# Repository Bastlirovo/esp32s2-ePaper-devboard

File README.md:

# esp32s2-ePaper-devboard
Development board for ESP32-S2, with two LDO options, two Li-ion charger options and ePaper connection part.

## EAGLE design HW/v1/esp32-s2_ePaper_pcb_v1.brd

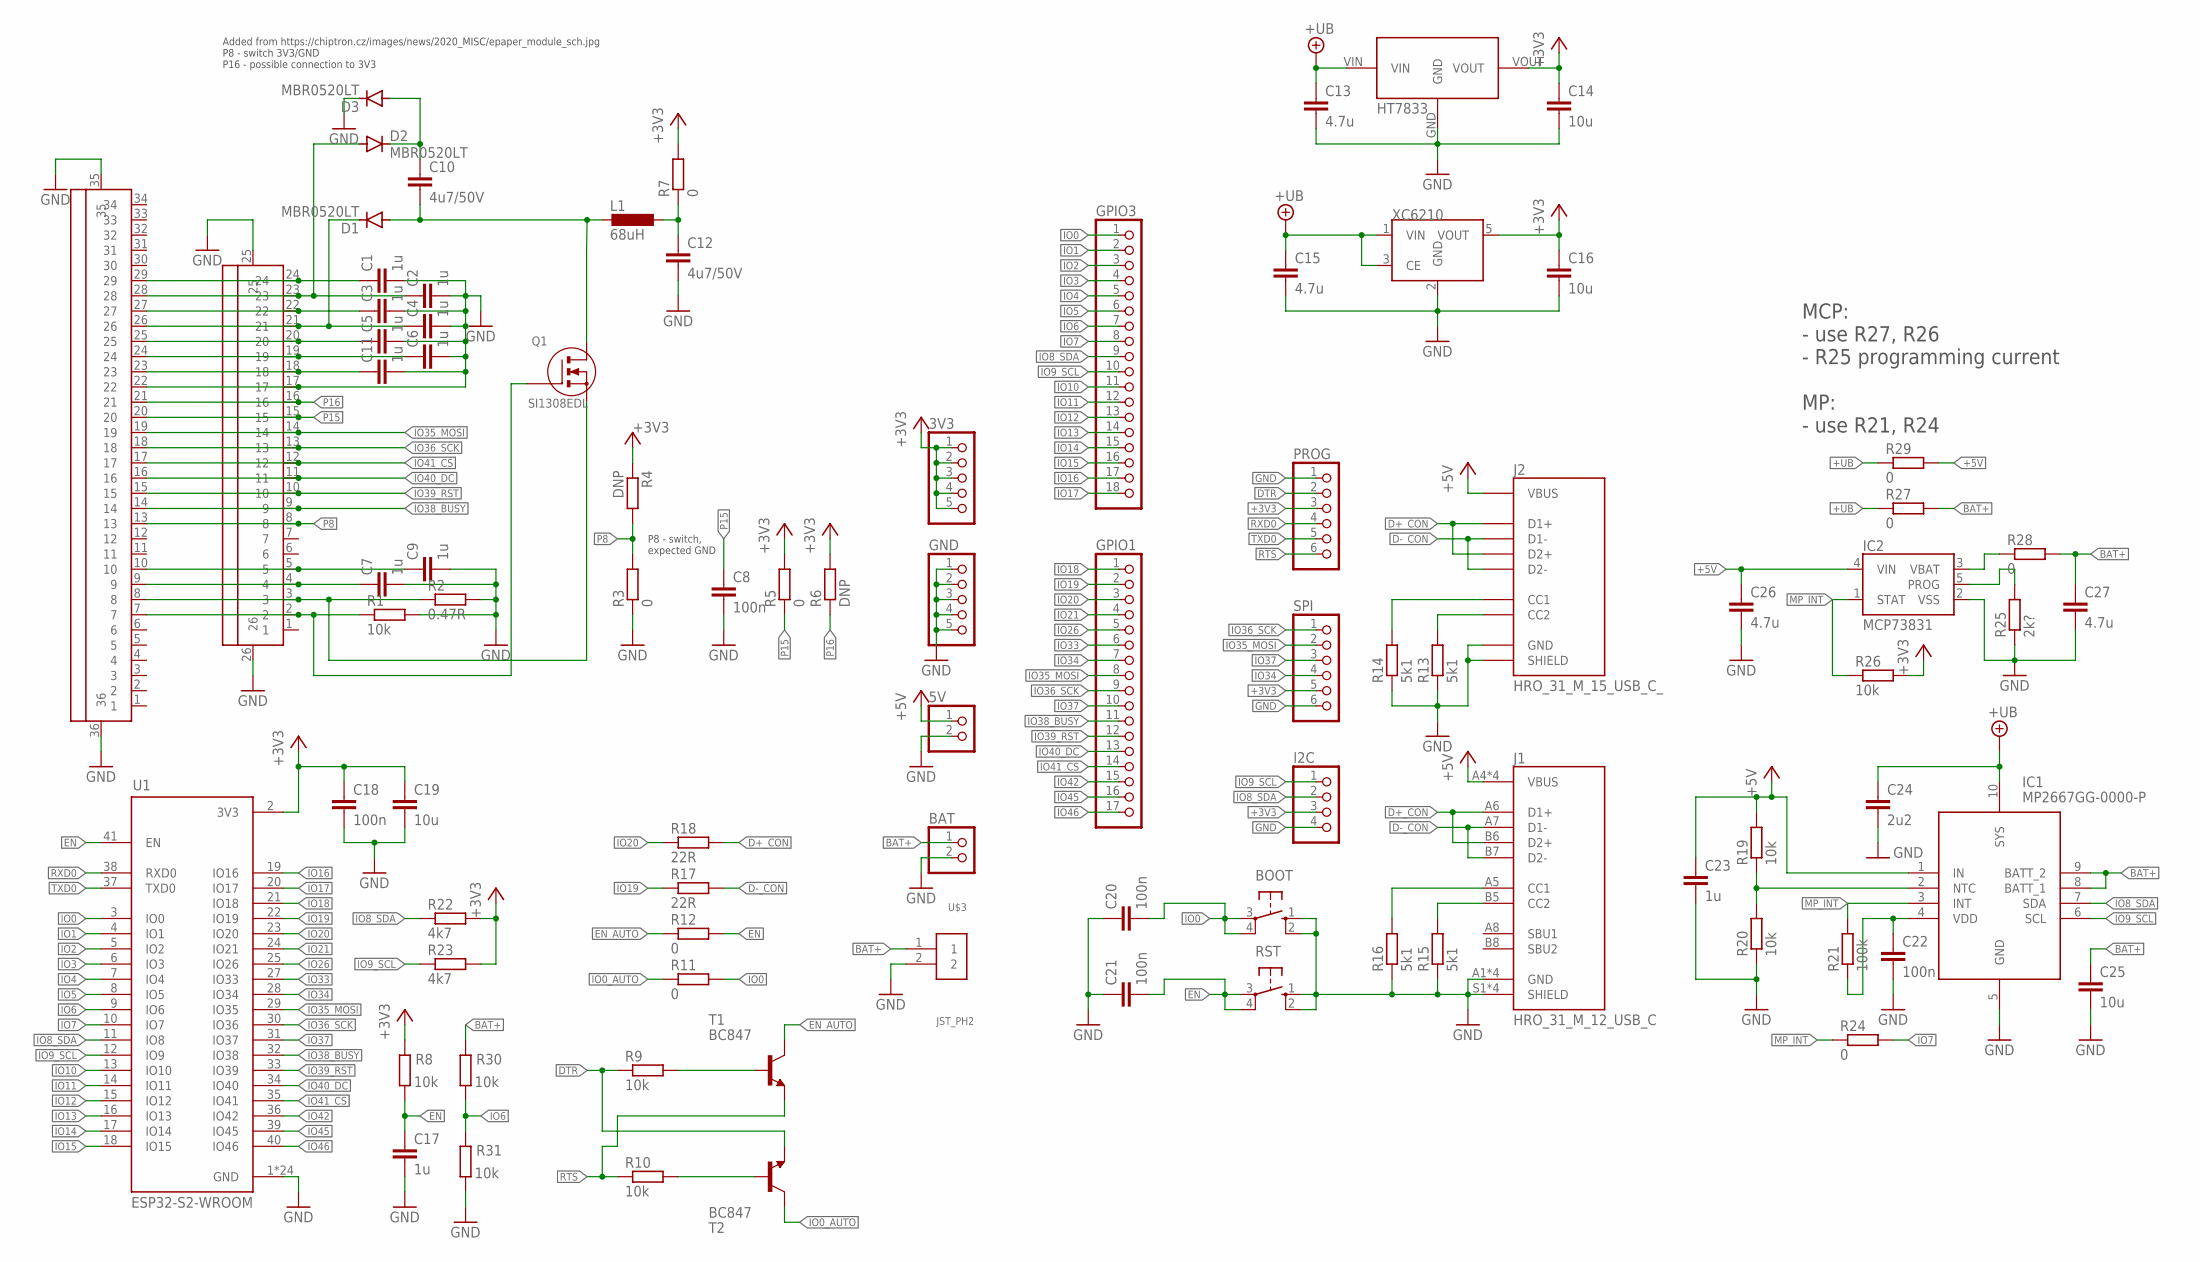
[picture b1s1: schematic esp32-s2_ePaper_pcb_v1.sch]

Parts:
3V3: PINHD-1X5; 1X05
5V: PINHD-1X2; 1X02
BAT: PINHD-1X2; 1X02
BOOT: 10-XX; B3F-10XX
C1, C2, C3, C4, C5, C6, C7, C9, C11, C17, C23: 1u; C0603K
C8, C18, C20, C21, C22: 100n; C0603K
C10, C12: 4u7/50V; C1206
C13, C15, C26, C27: 4.7u; C1206
C14, C16, C19, C25: 10u; C1206
C24: 2u2; C1206
D1, D2, D3: MBR0520LT; SOD123
GND: PINHD-1X5; 1X05
GPIO1: PINHD-1X17; 1X17
GPIO3: PINHD-1X18; 1X18
I2C: PINHD-1X4; 1X04
IC1: MP2667GG-0000-P; QFN50P200X200X105-10N
IC2: MCP73831; SOT95P290X120-5
J1: HRO_31_M_12_USB_C
J2: HRO_31_M_15_USB_C_; HRO_31_M_15_USB_C
L1: 68uH; L4532P
PROG: PINHD-1X6; 1X06
Q1: SI1308EDL; SC-70
R1, R8, R9, R10, R19, R20, R26, R30, R31: 10k; R0603
R2: 0.47R; R0603
R3, R5, R7, R11, R12, R24, R27, R28, R29: 0; R0603
R4, R6: DNP; R0603
R13, R14, R15, R16: 5k1; R0603
R17, R18: 22R; R0603
R21: 100k; R0603
R22, R23: 4k7; R0603
R25: 2k?; R0603
RST: 10-XX; B3F-10XX
SPI: PINHD-1X6; 1X06
T1, T2: BC847; SOT23
U1: ESP32-S2-WROOM; XCVR_ESP32-S2-WROOM
U2: HT7833; SOT89
U3: XC6210; SOT-23-5
U$1: AYF532435_FPC_24PIN_0.5; FPC_0.5_24PIN
U$2: AYF533435_FPC_34PIN_0.5; FPC_0.5_34PIN
U$3: JST_PH2; JSTPH2

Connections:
+3V3: 3V3.1, 3V3.2, 3V3.3, 3V3.4, 3V3.5, C14.1, C16.1, C18.1, C19.1, I2C.3, PROG.3, R4.1, R5.2, R6.2, R7.2, R8.2, R22.2, R23.2, R26.2, SPI.5, U1.2 (3V3), U2.VOUT, U3.5 (VOUT)
+5V: 5V.1, C23.1, C26.1, IC1.1 (IN), IC2.4 (VIN), J1.A4 (VBUS), J1.A9 (VBUS), J1.B4 (VBUS), J1.B9 (VBUS), J2.P$2 (VBUS), J2.P$6 (VBUS), J2.P$9 (VBUS), J2.P$13 (VBUS), R19.2, R29.2
+UB: C13.1, C15.1, C24.1, IC1.10 (SYS), R27.1, R29.1, U2.VIN, U3.1 (VIN), U3.3 (CE)
BAT+: BAT.1, C25.1, C27.1, IC1.8 (BATT_1), IC1.9 (BATT_2), R27.2, R28.2, R30.2, U$3.1
D+_CON: J1.A6 (D1+), J1.B6 (D2+), J2.P$4 (D1+), J2.P$11 (D2+), R18.2
D-_CON: J1.A7 (D1-), J1.B7 (D2-), J2.P$3 (D1-), J2.P$10 (D2-), R17.2
DTR: PROG.2, R9.1, T2.2 (E)
EN: C17.1, C21.2, R8.1, R12.2, RST.3, RST.4 (P1), U1.41 (EN)
EN_AUTO: R12.1, T1.3 (C)
GND: 5V.2, BAT.2, BOOT.1 (S), BOOT.2 (S1), C1.2, C2.2, C3.2, C4.2, C5.2, C6.2, C7.2, C8.2, C9.2, C11.2, C12.2, C13.2, C14.2, C15.2, C16.2, C17.2, C18.2, C19.2, C20.1, C21.1, C22.2, C23.2, C24.2, C25.2, C26.2, C27.2, D3.C, GND.1, GND.2, GND.3, GND.4, GND.5, I2C.4, IC1.5 (GND), IC2.2 (VSS), J1.A1 (GND), J1.A12 (GND), J1.B1 (GND), J1.B12 (GND), J1.S1 (SHIELD), J1.S2 (SHIELD), J1.S3 (SHIELD), J1.S4 (SHIELD), J2.P$1 (GND), J2.P$7 (GND), J2.P$8 (GND), J2.P$14 (GND), J2.P$15 (SHIELD), J2.P$16 (SHIELD), J2.P$17 (SHIELD), J2.P$18 (SHIELD), PROG.1, R1.2, R2.2, R3.1, R13.1, R14.1, R15.1, R16.1, R20.1, R25.1, R31.1, RST.1 (S), RST.2 (S1), SPI.6, U1.1 (GND), U1.26 (GND), U1.42 (GND), U1.43.1 (GND), U1.43.2 (GND), U1.43.3 (GND), U1.43.4 (GND), U1.43.5 (GND), U1.43.6 (GND), U1.43.7 (GND), U1.43.8 (GND), U1.43.9 (GND), U1.43.10 (GND), U1.43.11 (GND), U1.43.12 (GND), U1.43.13 (GND), U1.43.14 (GND), U1.43.15 (GND), U1.43.16 (GND), U1.43.17 (GND), U1.43.18 (GND), U1.43.19 (GND), U1.43.20 (GND), U1.43.21 (GND), U2.GND, U3.2 (GND), U$1.17, U$1.25, U$1.26, U$2.22, U$2.35, U$2.36, U$3.2
IO0: BOOT.3, BOOT.4 (P1), C20.2, GPIO3.1, R11.2, U1.3 (IO0)
IO0_AUTO: R11.1, T2.3 (C)
IO1: GPIO3.2, U1.4 (IO1)
IO2: GPIO3.3, U1.5 (IO2)
IO3: GPIO3.4, U1.6 (IO3)
IO4: GPIO3.5, U1.7 (IO4)
IO5: GPIO3.6, U1.8 (IO5)
IO6: GPIO3.7, R30.1, R31.2, U1.9 (IO6)
IO7: GPIO3.8, R24.2, U1.10 (IO7)
IO8_SDA: GPIO3.9, I2C.2, IC1.7 (SDA), R22.1, U1.11 (IO8)
IO9_SCL: GPIO3.10, I2C.1, IC1.6 (SCL), R23.1, U1.12 (IO9)
IO10: GPIO3.11, U1.13 (IO10)
IO11: GPIO3.12, U1.14 (IO11)
IO12: GPIO3.13, U1.15 (IO12)
IO13: GPIO3.14, U1.16 (IO13)
IO14: GPIO3.15, U1.17 (IO14)
IO15: GPIO3.16, U1.18 (IO15)
IO16: GPIO3.17, U1.19 (IO16)
IO17: GPIO3.18, U1.20 (IO17)
IO18: GPIO1.1, U1.21 (IO18)
IO19: GPIO1.2, R17.1, U1.22 (IO19)
IO20: GPIO1.3, R18.1, U1.23 (IO20)
IO21: GPIO1.4, U1.24 (IO21)
IO26: GPIO1.5, U1.25 (IO26)
IO33: GPIO1.6, U1.27 (IO33)
IO34: GPIO1.7, SPI.4, U1.28 (IO34)
IO35_MOSI: GPIO1.8, SPI.2, U1.29 (IO35), U$1.14, U$2.19
IO36_SCK: GPIO1.9, SPI.1, U1.30 (IO36), U$1.13, U$2.18
IO37: GPIO1.10, SPI.3, U1.31 (IO37)
IO38_BUSY: GPIO1.11, U1.32 (IO38), U$1.9, U$2.14
IO39_RST: GPIO1.12, U1.33 (IO39), U$1.10, U$2.15
IO40_DC: GPIO1.13, U1.34 (IO40), U$1.11, U$2.16
IO41_CS: GPIO1.14, U1.35 (IO41), U$1.12, U$2.17
IO42: GPIO1.15, U1.36 (IO42)
IO45: GPIO1.16, U1.39 (IO45)
IO46: GPIO1.17, U1.40 (IO46)
MP_INT: IC1.3 (INT), IC2.1 (STAT), R21.2, R24.1, R26.1
unnamed: C1.1, U$1.24, U$2.29
unnamed: C2.1, D2.A, U$1.23, U$2.28
unnamed: C3.1, U$1.22, U$2.27
unnamed: C4.1, D1.C, U$1.21, U$2.26
unnamed: C5.1, U$1.20, U$2.25
unnamed: C6.1, U$1.19, U$2.24
unnamed: C11.1, U$1.18, U$2.23
unnamed: C12.1, L1.1, R7.1
unnamed: IC2.3 (VBAT), R28.1
unnamed: Q1.2 (S), R2.1, U$1.3, U$2.8
unnamed: C9.1, U$1.5, U$2.10
unnamed: C7.1, U$1.4, U$2.9
unnamed: Q1.1 (G), R1.1, U$1.2, U$2.7
unnamed: IC1.2 (NTC), R19.1, R20.2
unnamed: C10.1, D2.C, D3.A
unnamed: IC2.5 (PROG), R25.2
unnamed: C22.1, IC1.4 (VDD), R21.1
unnamed: C10.2, D1.A, L1.2, Q1.3 (D)
unnamed: J2.P$12 (CC2), R13.2
unnamed: J2.P$5 (CC1), R14.2
unnamed: J1.B5 (CC2), R15.2
unnamed: J1.A5 (CC1), R16.2
unnamed: R10.2, T2.1 (B)
unnamed: R9.2, T1.1 (B)
P8: R3.2, R4.2, U$1.8, U$2.13
P15: C8.1, R5.1, U$1.15, U$2.20
P16: R6.1, U$1.16, U$2.21
RTS: PROG.6, R10.1, T1.2 (E)
RXD0: PROG.4, U1.38 (RXD0)
TXD0: PROG.5, U1.37 (TXD0)

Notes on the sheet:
P8 - switch, expected GND
Added from https://chiptron.cz/images/news/2020_MISC/epaper_module_sch.jpg P8 - switch 3V3/GND P16 - possible connection to 3V3
MCP: - use R27, R26 - R25 programming current MP: - use R21, R24

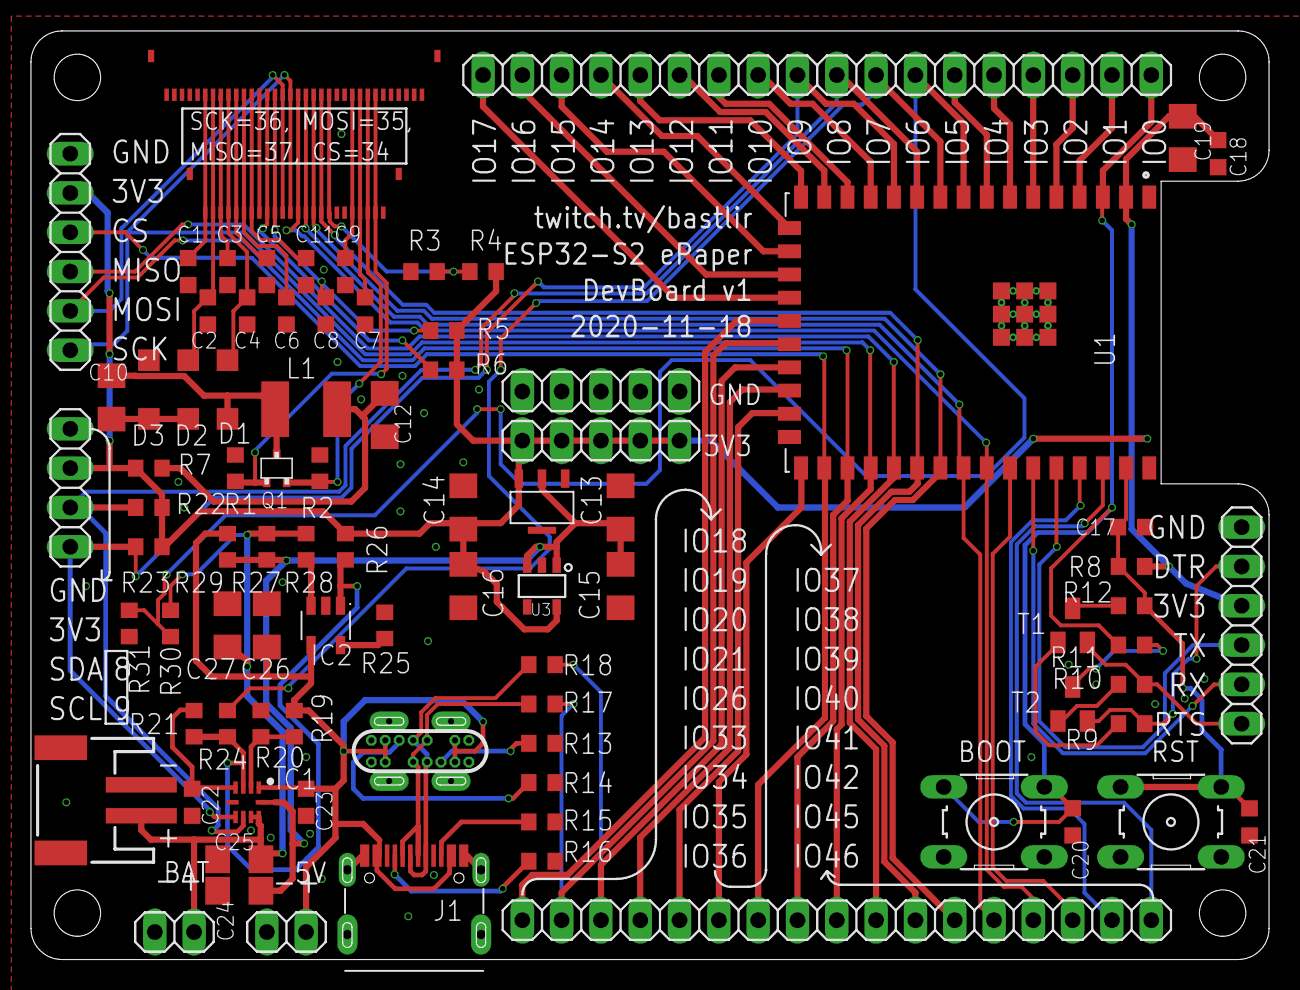
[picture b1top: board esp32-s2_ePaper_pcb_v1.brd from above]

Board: 2 copper layers, 80.0 x 60.0 mm, 86 parts (0 on the bottom side), 77 nets.

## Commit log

2020-12-15 Initial commit of HW v1
